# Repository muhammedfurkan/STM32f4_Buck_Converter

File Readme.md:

# STM32F4-Buck Converter

 KiCad + STM32F4 + USB + Buck converter 4 layer PCB design.

# Schematic Preview Image

# PCB Design Preview Image

# Info

You can contact with me from [Telegram](www.https//:t.me/By_Azade)

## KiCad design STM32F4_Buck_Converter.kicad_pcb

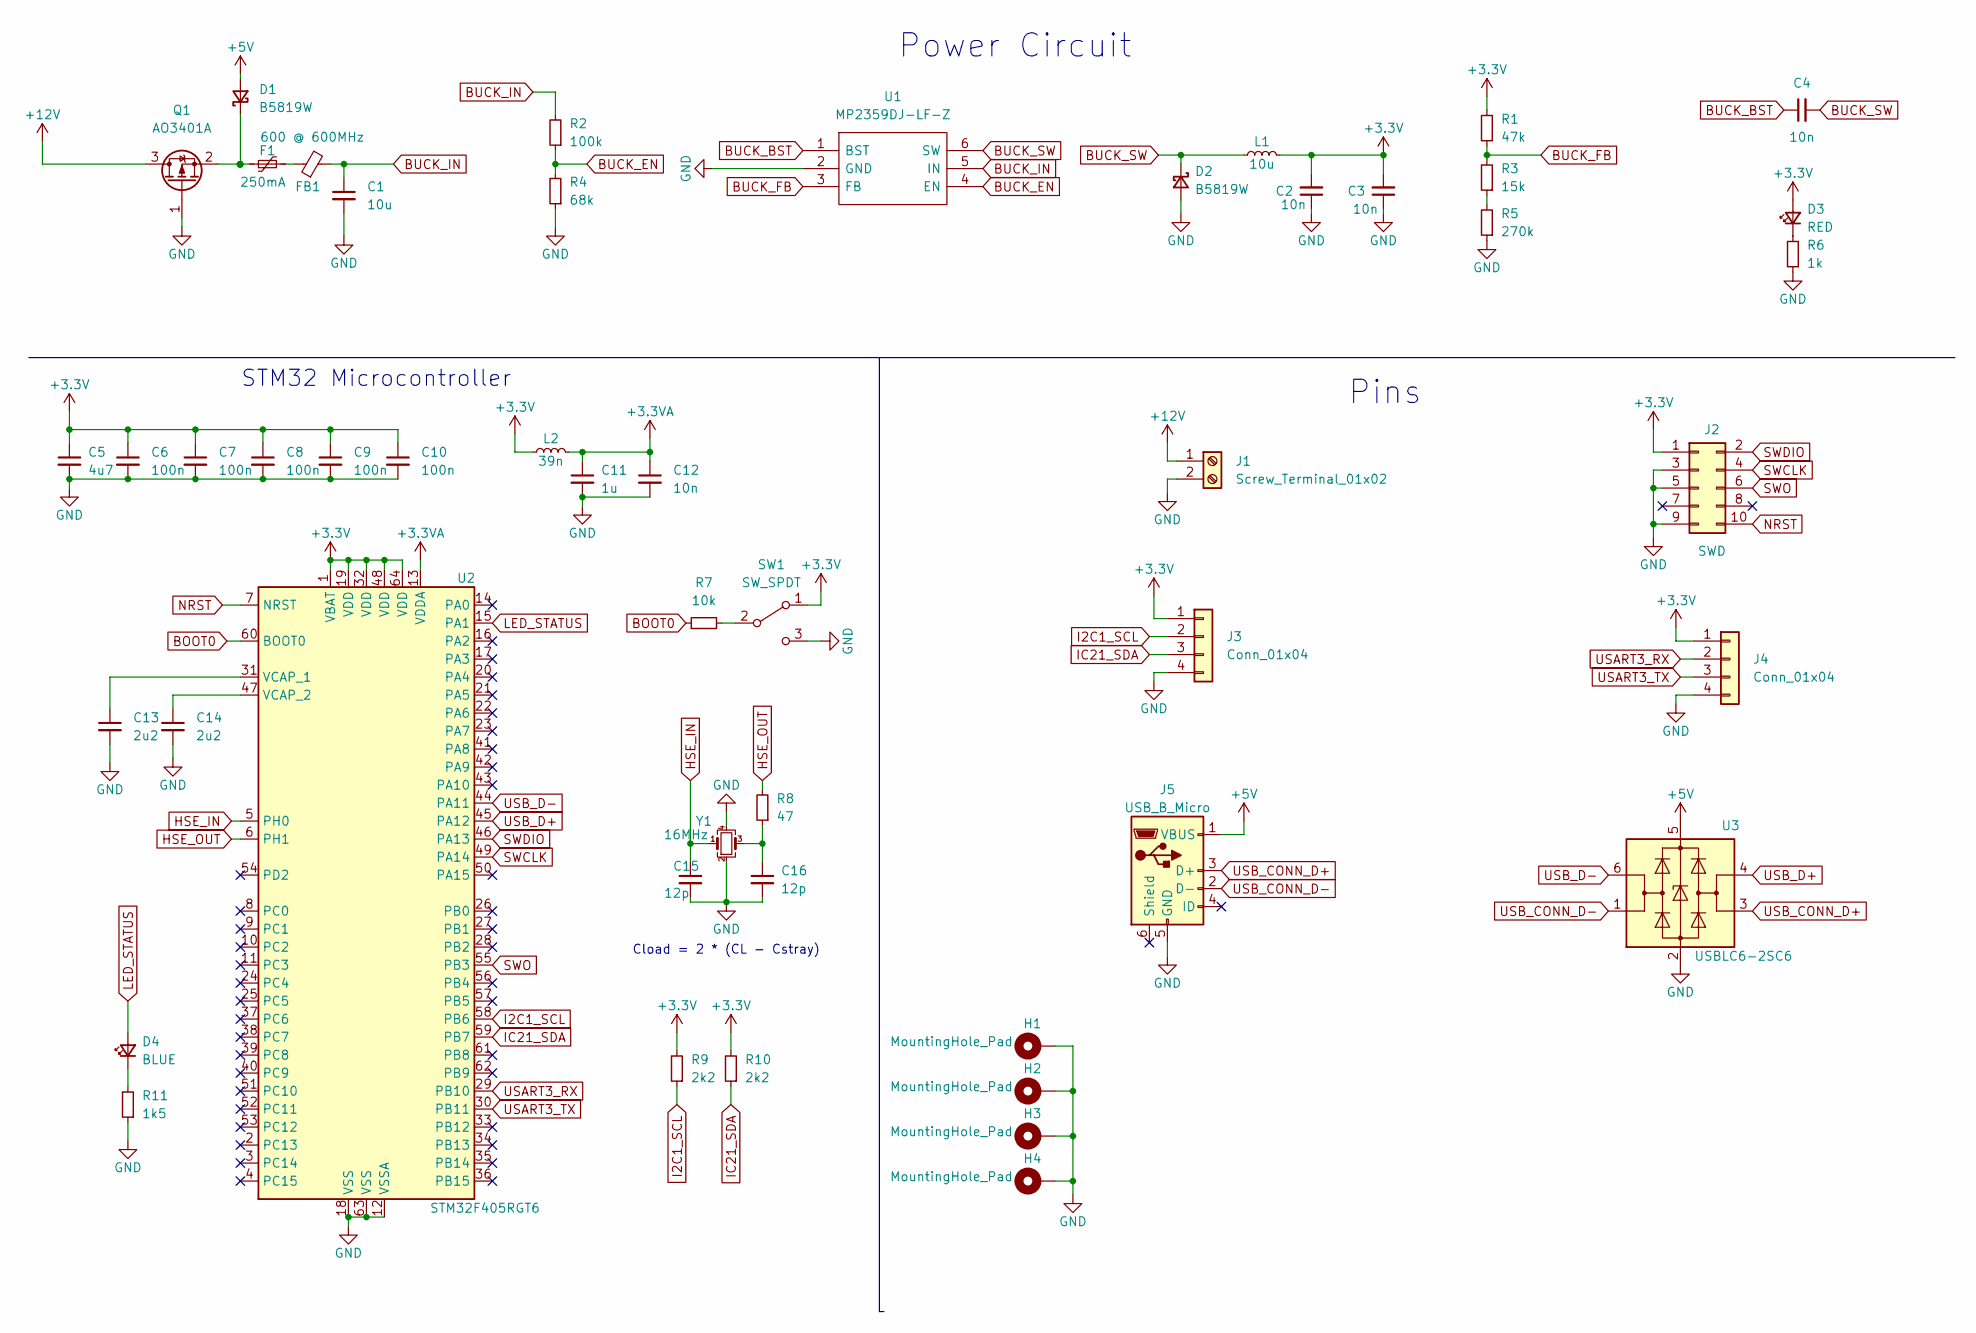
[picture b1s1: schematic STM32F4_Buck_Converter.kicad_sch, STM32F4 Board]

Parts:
C1: 10u; C_1206_3216Metric
C2, C3: 10n; C_1206_3216Metric
C4: 10n; C_0603_1608Metric
C5: 4u7; C_0603_1608Metric_Pad1.08x0.95mm_HandSolder
C6, C7, C8, C9, C10: 100n; C_0402_1005Metric
C11: 1u; C_0402_1005Metric
C12: 10n; C_0402_1005Metric
C13, C14: 2u2; C_0201_0603Metric
C15, C16: 12p; C_0402_1005Metric
D1, D2: B5819W; D_SOD-123
D3: RED; LED_0603_1608Metric
D4: BLUE; LED_0603_1608Metric
F1: 250mA; Fuse_1206_3216Metric
FB1: 600 @ 600MHz; L_0805_2012Metric
H1, H2, H3, H4: MountingHole_Pad; MountingHole_4.3mm_M4_Pad_Via
J1: Screw_Terminal_01x02; TerminalBlock_Phoenix_MKDS-1,5-2_1x02_P5.00mm_Horizontal
J2: SWD; PinHeader_2x05_P1.27mm_Vertical_SMD
J3, J4: Conn_01x04; Molex_PicoBlade_53048-0410_1x04_P1.25mm_Horizontal
J5: USB_B_Micro; USB_Micro-B_Molex_47346-0001
L1: 10u; L_TDK_SLF6025
L2: 39n; L_0402_1005Metric
Q1: AO3401A; SOT-23
R1: 47k; R_0603_1608Metric
R2: 100k; R_0603_1608Metric
R3: 15k; R_0603_1608Metric
R4: 68k; R_0603_1608Metric
R5: 270k; R_0603_1608Metric
R6: 1k; R_0603_1608Metric
R7: 10k; R_0402_1005Metric
R8: 47; R_0402_1005Metric
R9, R10: 2k2; R_0402_1005Metric
R11: 1k5; R_0402_1005Metric
SW1: SW_SPDT; SW_SPDT_PCM12
U1: MP2359DJ-LF-Z; SOT-23-6; Manufacturer_Part_Number MP2359DJ-LF-Z; Mouser Part Number 946-MP2359DJLFZ
U2: STM32F405RGT6; LQFP-64_10x10mm_P0.5mm
U3: USBLC6-2SC6; SOT-23-6
Y1: 16MHz; Crystal_SMD_3225-4Pin_3.2x2.5mm

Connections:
+3.3VA: C11.1, C12.1, L2.2, U2.13 (VDDA)
+3V3: C2.2, C3.2, C5.1, C6.1, C7.1, C8.1, C9.1, C10.1, D3.2 (A), J2.1, J3.1, J4.1, L1.2, L2.1, R1.2, R9.2, R10.2, SW1.1 (A), U2.1 (VBAT), U2.19 (VDD), U2.32 (VDD), U2.48 (VDD), U2.64 (VDD)
+5V: D1.2 (A), J5.1 (VBUS), U3.5 (VBUS)
+12V: J1.1, Q1.3 (D); also elsewhere on the board
BOOT0: R7.1, U2.60 (BOOT0)
BUCK_BST: C4.1, U1.1 (BST)
BUCK_EN: R2.1, R4.2, U1.4 (EN)
BUCK_FB: R1.1, R3.2, U1.3 (FB)
BUCK_IN: C1.1, FB1.2, R2.2, U1.5 (IN)
BUCK_SW: C4.2, D2.1 (K), L1.1, U1.6 (SW)
GND: C1.2, C2.1, C3.1, C5.2, C6.2, C7.2, C8.2, C9.2, C10.2, C11.2, C12.2, C13.2, C14.2, C15.2, C16.2, D2.2 (A), H1.1, H2.1, H3.1, H4.1, J1.2, J2.3, J2.5, J2.9, J3.4, J4.4, J5.5 (GND), Q1.1 (G), R4.1, R5.1, R6.1, R11.1, SW1.3 (C), U1.2 (GND), U2.12 (VSSA), U2.18 (VSS), U2.63 (VSS), U3.2 (GND), Y1.2, Y1.4
HSE_IN: C15.1, U2.5 (PH0), Y1.1
HSE_OUT: R8.2, U2.6 (PH1)
I2C1_SCL: J3.2, R9.1, U2.58 (PB6)
IC21_SDA: J3.3, R10.1, U2.59 (PB7)
LED_STATUS: D4.2 (A), U2.15 (PA1)
NRST: J2.10, U2.7 (NRST)
unnamed: C13.1, U2.31 (VCAP_1)
unnamed: C14.1, U2.47 (VCAP_2)
unnamed: C16.1, R8.1, Y1.3
unnamed: D1.1 (K), F1.1, Q1.2 (S)
unnamed: D3.1 (K), R6.2
unnamed: D4.1 (K), R11.2
unnamed: F1.2, FB1.1
unnamed: R3.1, R5.2
unnamed: R7.2, SW1.2 (B)
SWCLK: J2.4, U2.49 (PA14)
SWDIO: J2.2, U2.46 (PA13)
SWO: J2.6, U2.55 (PB3)
USART3_RX: J4.2, U2.29 (PB10)
USART3_TX: J4.3, U2.30 (PB11)
USB_CONN_D+: J5.3 (D+), U3.3 (I/O2)
USB_CONN_D-: J5.2 (D-), U3.1 (I/O1)
USB_D+: U2.45 (PA12), U3.4 (I/O2)
USB_D-: U2.44 (PA11), U3.6 (I/O1)

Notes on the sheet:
Cload = 2 * (CL - Cstray)
Pins
Power Circuit
STM32 Microcontroller

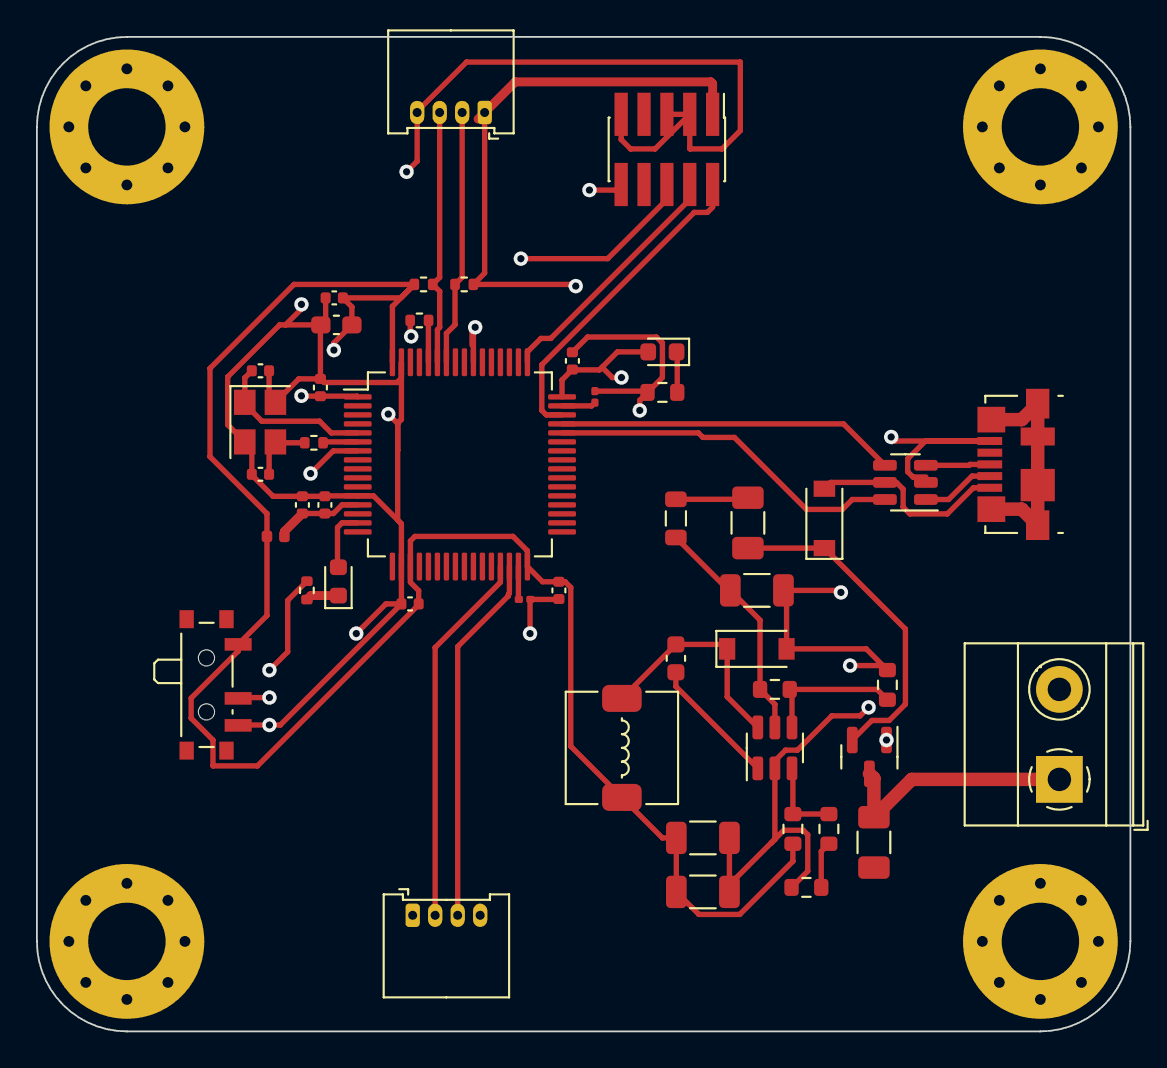
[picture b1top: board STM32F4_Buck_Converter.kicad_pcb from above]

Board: 4 copper layers, 60.8 x 55.2 mm, 51 parts (0 on the bottom side), 35 nets.

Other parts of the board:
F1#2: 250mA; Fuse_1206_3216Metric

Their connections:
+12V: F1#2.1; also elsewhere on the board

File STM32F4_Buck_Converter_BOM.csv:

"Id";"Designator";"Package";"Quantity";"Designation";"Supplier and ref";
1;"R2";"R_0603_1608Metric";1;"100k";;;
2;"C2,C3";"C_1206_3216Metric";2;"10n";;;
3;"R4";"R_0603_1608Metric";1;"68k";;;
4;"H4,H3,H2,H1";"MountingHole_4.3mm_M4_Pad_Via";4;"MountingHole_Pad";;;
5;"U2";"LQFP-64_10x10mm_P0.5mm";1;"STM32F405RGT6";;;
6;"C10,C7,C9,C6,C8";"C_0402_1005Metric";5;"100n";;;
7;"C5";"C_0603_1608Metric_Pad1.08x0.95mm_HandSolder";1;"4u7";;;
8;"D3";"LED_0603_1608Metric";1;"RED";;;
9;"C16,C15";"C_0402_1005Metric";2;"12p";;;
10;"U3";"SOT-23-6";1;"USBLC6-2SC6";;;
11;"C4";"C_0603_1608Metric";1;"10n";;;
12;"Q1";"SOT-23";1;"AO3401A";;;
13;"D1,D2";"D_SOD-123";2;"B5819W";;;
14;"R11";"R_0402_1005Metric";1;"1k5";;;
15;"C1";"C_1206_3216Metric";1;"10u";;;
16;"J1";"TerminalBlock_Phoenix_MKDS-1,5-2_1x02_P5.00mm_Horizontal";1;"Screw_Terminal_01x02";;;
17;"R6";"R_0603_1608Metric";1;"1k";;;
18;"R7";"R_0402_1005Metric";1;"10k";;;
19;"J3,J4";"Molex_PicoBlade_53048-0410_1x04_P1.25mm_Horizontal";2;"Conn_01x04";;;
20;"C14,C13";"C_0201_0603Metric";2;"2u2";;;
21;"R8";"R_0402_1005Metric";1;"47";;;
22;"SW1";"SW_SPDT_PCM12";1;"SW_SPDT";;;
23;"R9,R10";"R_0402_1005Metric";2;"2k2";;;
24;"F1,F1";"Fuse_1206_3216Metric";2;"250mA";;;
25;"Y1";"Crystal_SMD_3225-4Pin_3.2x2.5mm";1;"16MHz";;;
26;"D4";"LED_0603_1608Metric";1;"BLUE";;;
27;"FB1";"L_0805_2012Metric";1;"600 @ 600MHz";;;
28;"R3";"R_0603_1608Metric";1;"15k";;;
29;"U1";"SOT-23-6";1;"MP2359DJ-LF-Z";;;
30;"L2";"L_0402_1005Metric";1;"39n";;;
31;"R1";"R_0603_1608Metric";1;"47k";;;
32;"C12";"C_0402_1005Metric";1;"10n";;;
33;"J5";"USB_Micro-B_Molex_47346-0001";1;"USB_B_Micro";;;
34;"L1";"L_TDK_SLF6025";1;"10u";;;
35;"R5";"R_0603_1608Metric";1;"270k";;;
36;"J2";"PinHeader_2x05_P1.27mm_Vertical_SMD";1;"SWD";;;
37;"C11";"C_0402_1005Metric";1;"1u";;;
